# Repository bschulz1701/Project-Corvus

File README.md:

# Project-Corvus
Designs for multiple lab voltage/current sensor variations

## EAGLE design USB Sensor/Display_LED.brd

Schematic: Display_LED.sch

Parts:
BT1: AACLIP; BAT_AA_BK-92
C1, C2: C-EU12PFC0402; C0402
C3, C4, C11, C12: 0.1uF; C0603
C5, C10, C13: 1uF; C0603
C6: 10uF; C0805
C7: 10pF; C0603
C8, C9: 4.7uF; C0805
D1, D2, D3, D4, D5, D6, D7, D8, D9, D10, D11, D12, D13: LED0603; LED_0603
DS1, DS2: YSD-439AK2B-35; 7-SEGMENT-4DIGIT-YOUNGSUN
H1, H2, H3, H4, H5: MOUNTING_HOLE2_NP; 2_56
ISP1, ISP2, ISP3: AVRISP-6; AVRISP
J1: CONN_2X2MIRCOFIT_RT; 2X2_MICROFIT_RT
L1: INDUCTORMAPI_3X3; WE-MAPI(3X3)
Q1, Q2, Q3, Q4, Q13, Q14, Q15, Q16: MOSFET-NCH-2N7002P; SOT23-3
Q5: MOSFET-NCH-ZXMN3B14FTA; SOT23-3
R1, R2, R25: R-EU_10KR0603; R0603
R3, R4, R5, R6, R7, R8, R9, R10, R22, R24: 100k; R0603
R11, R37, R45: 10k; R0603
R12, R13, R14, R15, R16, R17, R18, R19, R20, R21, R26, R27, R28, R29, R30, R31, R32, R33, R35, R36, R38, R39, R46, R47, R48, R49, R50, R51, R52, R53, R54, R55: R-EU_330R0603; R0603
R23: 316k; R0603
R34: 330R; R0603
R40: R-EU_1KR0603; R0603
S1: DIP_8219_GULL; 219-8_GULLWING_DIP-CTS
S2, S3, S4: BUTTON6X6; SWITCH_6MM
S5: SPDTOS1020; OS102011MS2QN1
U1: ATMEGA644M; MLF44-TH
U2: SN74HC165PW; TSSOP16
U4, U7: ATMEGA48PMLF; MLF32-5X5
U5: TPS61021A; DSG0008A
XTAL1: CRYSTAL8MHZ5X3.2; CRYSTAL_5X3.2_2-SMD

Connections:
3V3: C3.1, C4.1, C5.1, C7.1, C8.1, C9.1, C10.1, C11.1, C12.1, C13.1, ISP1.2 (VCC), ISP2.2 (VCC), ISP3.2 (VCC), J1.1, R1.2, R2.2, R3.2, R4.2, R5.2, R6.2, R7.2, R8.2, R9.2, R10.2, R11.2, R23.2, R25.2, R35.2, R37.2, R45.2, U1.5 (VCC), U1.17 (VCC), U1.27 (AVCC), U1.29 (AREF), U1.38 (VCC), U2.16 (VCC), U4.4 (VCC), U4.6 (VCC), U4.18 (AVCC), U4.20 (AREF), U5.3 (VOUT), U5.4 (VOUT), U7.4 (VCC), U7.6 (VCC), U7.18 (AVCC), U7.20 (AREF)
!RESET: ISP1.5 (RST), R37.1, U1.4 (RESET)
!RESET_A: ISP2.5 (RST), R11.1, U4.29 ((PCINT14/!RESET!)PC6)
!RESET_B: ISP3.5 (RST), R45.1, U7.29 ((PCINT14/!RESET!)PC6)
B0: R3.1, S1.16, U2.11 (A)
B1: R4.1, S1.15, U2.12 (B)
B2: R5.1, S1.14, U2.13 (C)
B3: R6.1, S1.13, U2.14 (D)
B4: R7.1, S1.12, U2.3 (E)
B5: R8.1, S1.11, U2.4 (F)
B6: R9.1, S1.10, U2.5 (G)
B7: R10.1, S1.9, U2.6 (H)
BAT: BT1.POS@1 (+), BT1.POS@2 (+), C6.1, L1.P$1 (1), Q5.1 (G), R34.2, R40.2, S5.1 (O), U5.8 (VIN)
BAT_SENSE: R40.1, U1.37 ((PCINT0/ADC0)PA0)
BOOST_EN: R22.2, S5.2, U5.5 (EN)
DIP_CLK: U1.32 ((PCINT5/ADC5)PA5), U2.2 (CLK)
DIP_LD: U1.31 ((PCINT6/ADC6)PA6), U2.1 (SH/!LD)
DIP_OUT: U1.33 ((PCINT4/ADC4)PA4), U2.9 (QH)
DISP_SEL_A: R1.1, S2.1, S2.2, U1.25 ((PCINT22/TOSC1)PC6)
DISP_SEL_B: R2.1, S3.1, S3.2, U1.26 ((PCINT23/TOSC2)PC7)
DISP_STAT_D1_A: R28.2, U1.14 ((PCINT29/OC1A)PD5)
DISP_STAT_D1_B: R32.2, U1.22 ((PCINT19/TMS)PC3)
DISP_STAT_D2_A: R29.2, U1.13 ((PCINT28/OC1B)PD4)
DISP_STAT_D2_B: R33.2, U1.21 ((PCINT18/TCK)PC2)
DISP_STAT_I_A: R27.2, U1.15 ((PCINT30/OC2B/ICP)PD6)
DISP_STAT_I_B: R31.2, U1.23 ((PCINT20/TDO)PC4)
DISP_STAT_V_A: R26.2, U1.16 ((PCINT31/OC2A)PD7)
DISP_STAT_V_B: R30.2, U1.24 ((PCINT21/TDI)PC5)
DIS_A1: DS1.14 (A), R12.1
DIS_A2: DS2.14 (A), R46.1
DIS_B1: DS1.16 (B), R13.1
DIS_B2: DS2.16 (B), R47.1
DIS_C1: DS1.13 (C), R14.1
DIS_C2: DS2.13 (C), R48.1
DIS_COL1: DS1.12 (COL-C), R20.1
DIS_COL2: DS2.12 (COL-C), R54.1
DIS_D1: DS1.3 (D), R15.1
DIS_D2: DS2.3 (D), R49.1
DIS_DIG1_1: DS1.1 (DIG1), Q1.3 (D)
DIS_DIG1_2: DS2.1 (DIG1), Q13.3 (D)
DIS_DIG2_1: DS1.2 (DIG2), Q2.3 (D)
DIS_DIG2_2: DS2.2 (DIG2), Q14.3 (D)
DIS_DIG3_1: DS1.6 (DIG3), Q3.3 (D)
DIS_DIG3_2: DS2.6 (DIG3), Q15.3 (D)
DIS_DIG4_1: DS1.8 (DIG4), Q4.3 (D)
DIS_DIG4_2: DS2.8 (DIG4), Q16.3 (D)
DIS_DP1: DS1.7 (DP), R19.1
DIS_DP2: DS2.7 (DP), R53.1
DIS_E1: DS1.5 (E), R16.1
DIS_E2: DS2.5 (E), R50.1
DIS_F1: DS1.11 (F), R17.1
DIS_F2: DS2.11 (F), R51.1
DIS_G1: DS1.15 (G), R18.1
DIS_G2: DS2.15 (G), R52.1
DIS_POS1: DS1.9 (APOS-C), R21.1
DIS_POS2: DS2.9 (APOS-C), R55.1
FB: C7.2, R23.1, R24.2, U5.2 (FB)
GND: C1.1, C2.1, C3.2, C4.2, C5.2, C6.2, C8.2, C9.2, C10.2, C11.2, C12.2, C13.2, D1.CATHODE, D2.CATHODE, D3.CATHODE, D4.CATHODE, D5.CATHODE, D6.CATHODE, D7.CATHODE, D8.CATHODE, D10.CATHODE, D11.CATHODE, D12.CATHODE, D13.CATHODE, DS1.4 (COL-A), DS1.10 (APOS-A), DS2.4 (COL-A), DS2.10 (APOS-A), ISP1.6 (GND), ISP2.6 (GND), ISP3.6 (GND), J1.2, Q1.2 (S), Q2.2 (S), Q3.2 (S), Q4.2 (S), Q5.2 (S), Q13.2 (S), Q14.2 (S), Q15.2 (S), Q16.2 (S), R22.1, R24.1, S1.1, S1.2, S1.3, S1.4, S1.5, S1.6, S1.7, S1.8, S2.3, S2.4, S3.3, S3.4, S4.3, S4.4, S5.3 (S), U1.6 (GND), U1.18 (GND), U1.28 (GND), U1.39 (GND), U1.TH (EXP), U2.8 (GND), U2.10 (SER), U4.3 (GND), U4.5 (GND), U4.21 (GND), U4.TH (GND), U5.1 (AGND), U5.EP@1 (PGND), U5.EP@2 (PGND), U5.EP@3 (PGND), U7.3 (GND), U7.5 (GND), U7.21 (GND), U7.TH (GND)
HOLD: R25.1, S4.1, S4.2, U1.30 ((PCINT7/ADC7)PA7)
MCU_A1: R12.2, U4.32 ((PCINT18/INT0)PD2)
MCU_A2: R46.2, U7.32 ((PCINT18/INT0)PD2)
MCU_B1: R13.2, U4.1 ((PCINT19/INT1)PD3)
MCU_B2: R47.2, U7.1 ((PCINT19/INT1)PD3)
MCU_C1: R14.2, U4.2 ((PCINT20/XCK/T0)PD4)
MCU_C2: R48.2, U7.2 ((PCINT20/XCK/T0)PD4)
MCU_COL1: R20.2, U4.12 ((PCINT0/CLKO/ICP1)PB0)
MCU_COL2: R54.2, U7.12 ((PCINT0/CLKO/ICP1)PB0)
MCU_D1: R15.2, U4.9 ((PCINT21/OC0B/T1)PD5)
MCU_D2: R49.2, U7.9 ((PCINT21/OC0B/T1)PD5)
MCU_DIG1_1: Q1.1 (G), U4.26 ((PCINT11/ADC3)PC3)
MCU_DIG1_2: Q13.1 (G), U7.26 ((PCINT11/ADC3)PC3)
MCU_DIG2_1: Q2.1 (G), U4.25 ((PCINT10/ADC2)PC2)
MCU_DIG2_2: Q14.1 (G), U7.25 ((PCINT10/ADC2)PC2)
MCU_DIG3_1: Q3.1 (G), U4.24 ((PCINT9/ADC1)PC1)
MCU_DIG3_2: Q15.1 (G), U7.24 ((PCINT9/ADC1)PC1)
MCU_DIG4_1: Q4.1 (G), U4.23 ((PCINT8/ADC0)PC0)
MCU_DIG4_2: Q16.1 (G), U7.23 ((PCINT8/ADC0)PC0)
MCU_DP1: R19.2, U4.14 ((PCINT2/!SS!/OC1B)PB2)
MCU_DP2: R53.2, U7.14 ((PCINT2/!SS!/OC1B)PB2)
MCU_E1: R16.2, U4.10 ((PCINT22/OC0A/AIN0)PD6)
MCU_E2: R50.2, U7.10 ((PCINT22/OC0A/AIN0)PD6)
MCU_F1: R17.2, U4.11 ((PCINT23/AIN1)PD7)
MCU_F2: R51.2, U7.11 ((PCINT23/AIN1)PD7)
MCU_G1: R18.2, U4.7 ((PCINT6/XTAL1/TOSC1)PB6)
MCU_G2: R52.2, U7.7 ((PCINT6/XTAL1/TOSC1)PB6)
MCU_POS1: R21.2, U4.13 ((PCINT1/OC1A)PB1)
MCU_POS2: R55.2, U7.13 ((PCINT1/OC1A)PB1)
MISO: ISP1.1 (MISO), U1.2 ((PCINT14/MISO)PB6)
MISO_A: ISP2.1 (MISO), U4.16 ((PCINT4/MISO)PB4)
MISO_B: ISP3.1 (MISO), U7.16 ((PCINT4/MISO)PB4)
MOSI: ISP1.4 (MOSI), U1.1 ((PCINT13/MOSI)PB5)
MOSI_A: ISP2.4 (MOSI), U4.15 ((PCINT3/OC2A/MOSI)PB3)
MOSI_B: ISP3.4 (MOSI), U7.15 ((PCINT3/OC2A/MOSI)PB3)
unnamed: D1.ANODE, R26.1
unnamed: D2.ANODE, R27.1
unnamed: D3.ANODE, R28.1
unnamed: D4.ANODE, R29.1
unnamed: D5.ANODE, R30.1
unnamed: D6.ANODE, R31.1
unnamed: D7.ANODE, R32.1
unnamed: D8.ANODE, R33.1
unnamed: D10.ANODE, R35.1
unnamed: BT1.NEG@1 (-), BT1.NEG@2 (-), D9.ANODE, Q5.3 (D)
unnamed: D9.CATHODE, R34.1
unnamed: D12.ANODE, R38.1
unnamed: C2.2, U1.8 (XTAL1), XTAL1.OSC1 (1)
unnamed: D11.ANODE, R36.1
unnamed: C1.2, U1.7 (XTAL2), XTAL1.OSC2 (2)
unnamed: D13.ANODE, R39.1
PG: R36.2, U1.36 ((PCINT1/ADC1)PA1)
RX1: U1.10 ((PCINT25/TXD0)PD1), U4.30 ((PCINT16/RXD)PD0)
RX2: U1.12 ((PCINT27/INT1)PD3), U7.30 ((PCINT16/RXD)PD0)
SCK: ISP1.3 (SCK), U1.3 ((PCINT15/SCK)PB7)
SCK_A: ISP2.3 (SCK), U4.17 ((PCINT5/SCK)PB5)
SCK_B: ISP3.3 (SCK), U7.17 ((PCINT5/SCK)PB5)
SCL: J1.3, U1.19 ((PCINT16/SCL)PC0)
SDA: J1.4, U1.20 ((PCINT17/SDA)PC1)
STAT1: R39.2, U1.35 ((PCINT2/ADC2)PA2)
STAT2: R38.2, U1.34 ((PCINT3/ADC3)PA3)
SW: L1.P$2 (2), U5.6 (SW), U5.7 (SW)
TX1: U1.9 ((PCINT24/RXD0)PD0), U4.31 ((PCINT17/TXD)PD1)
TX2: U1.11 ((PCINT26/INT0)PD2), U7.31 ((PCINT17/TXD)PD1)

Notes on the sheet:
Allow for additional bulk capacitance if needed
BAT - Analog PG - DO DIP_LD - DO DIP_CLK - DO DIP_OUT - DI DISP_SEL_A - DI DISP_SEL_B - DI HOLD - DI STAT1 - DO STAT2- DO

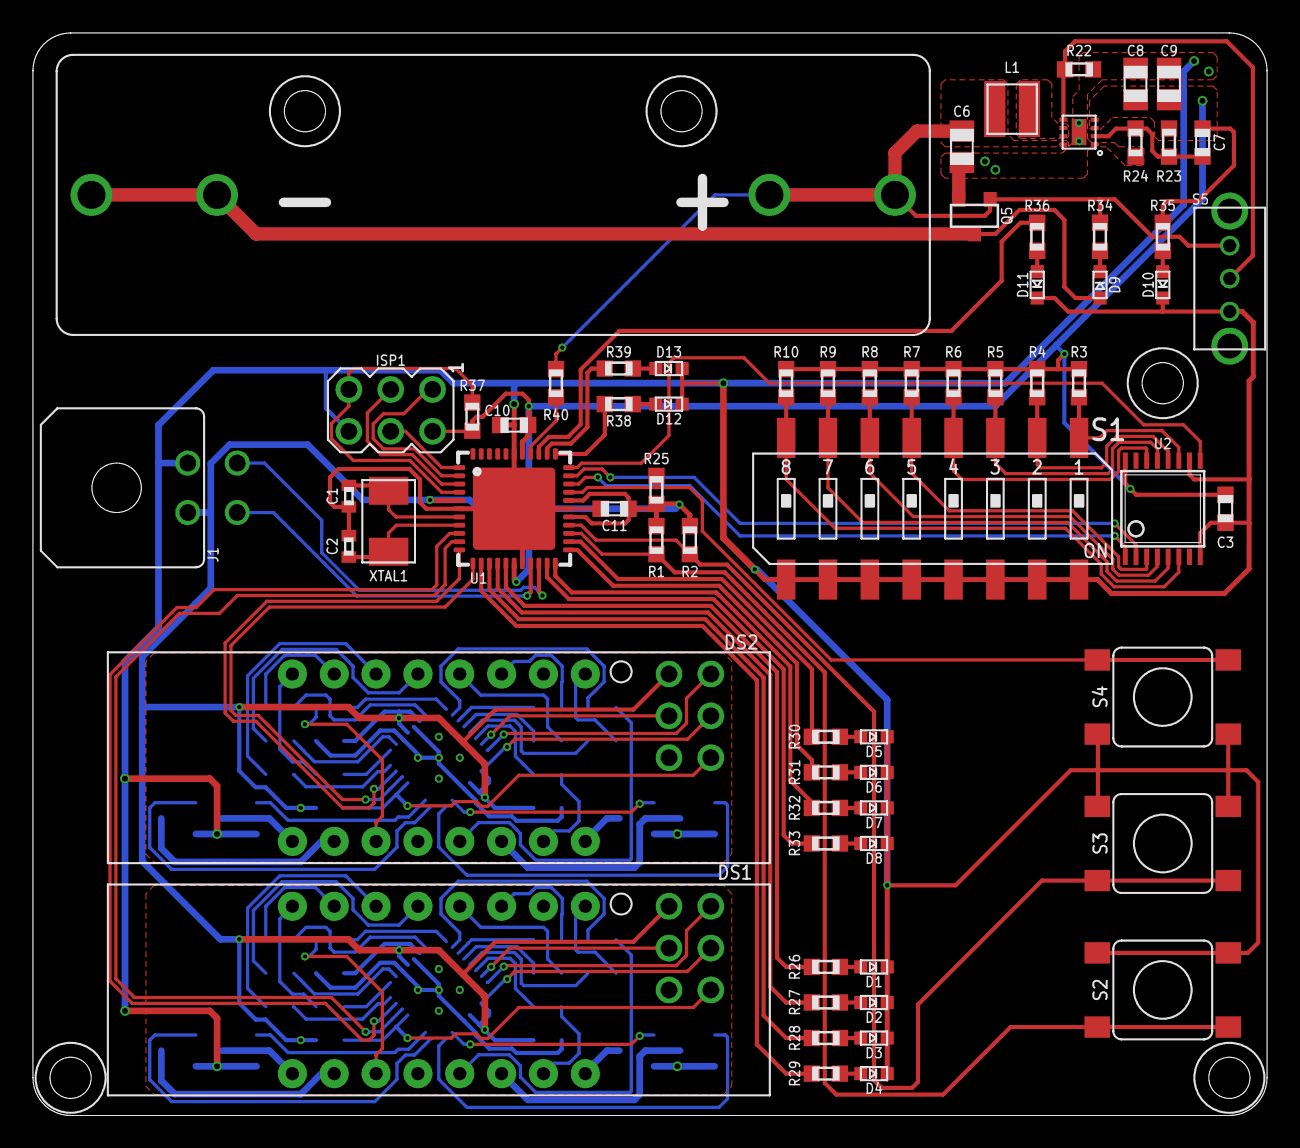
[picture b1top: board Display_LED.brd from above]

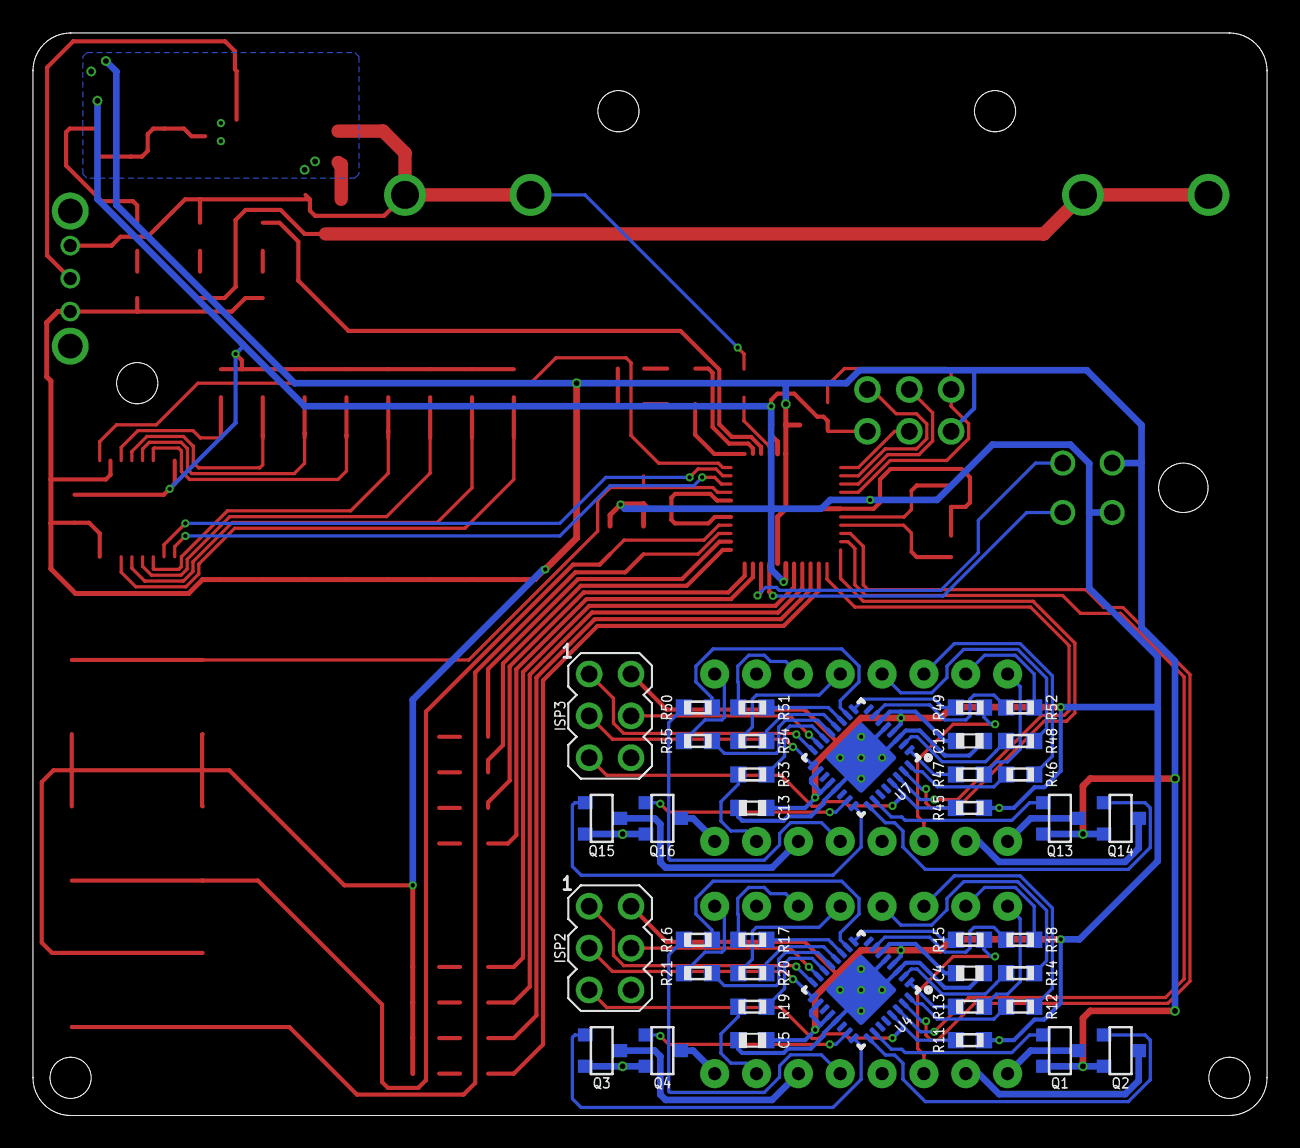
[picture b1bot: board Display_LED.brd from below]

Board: 2 copper layers, 74.9 x 65.7 mm, 110 parts (38 on the bottom side), 122 nets.

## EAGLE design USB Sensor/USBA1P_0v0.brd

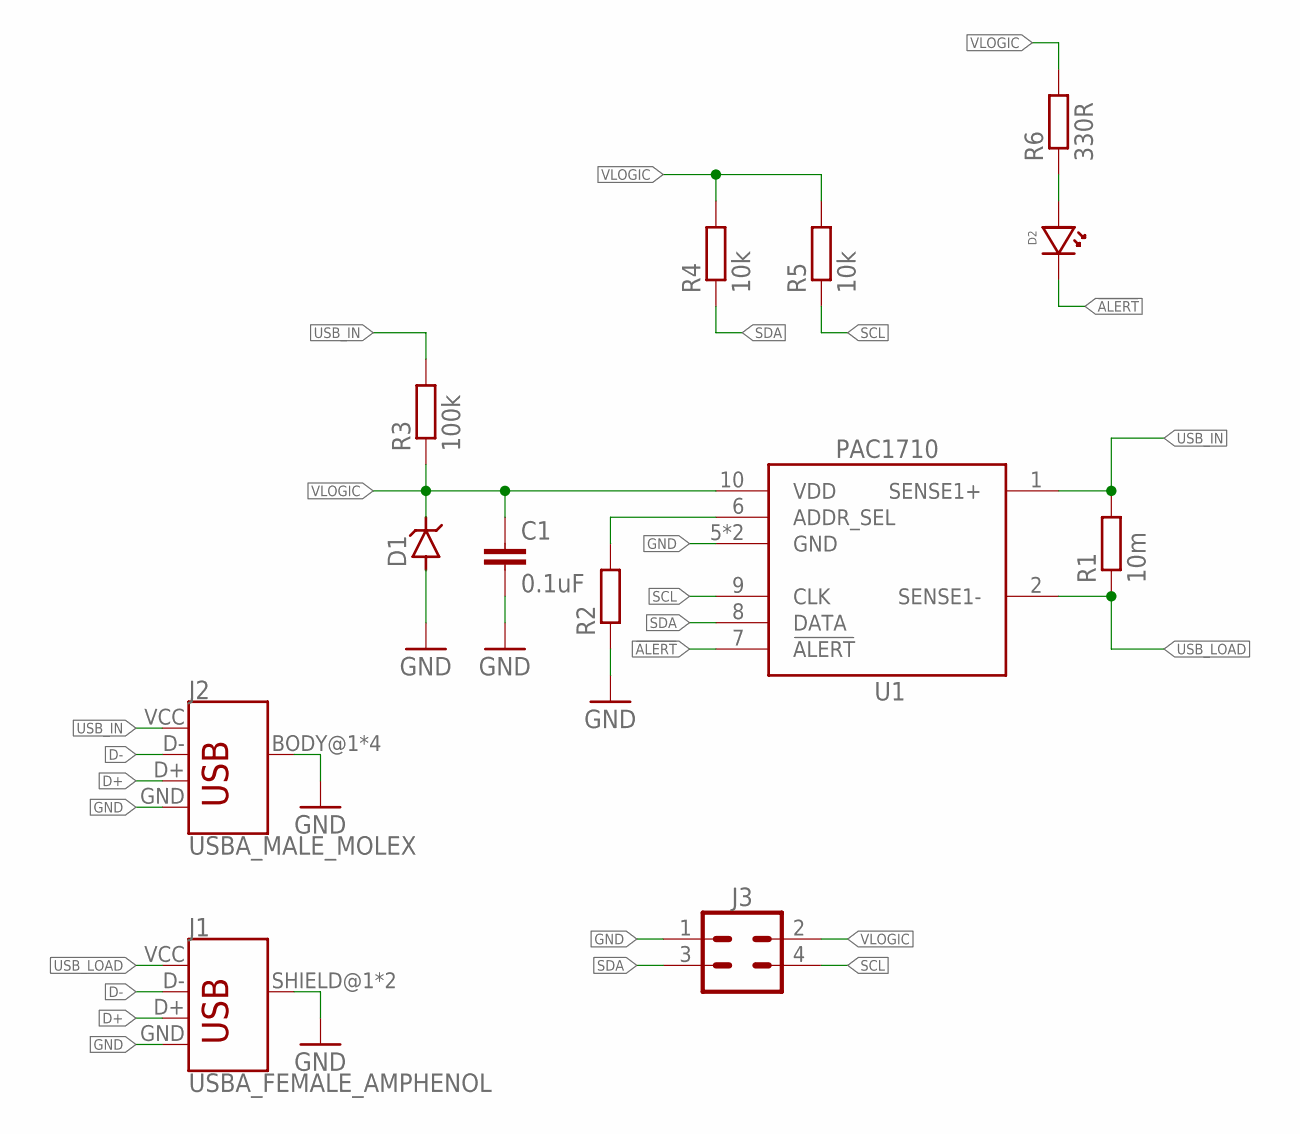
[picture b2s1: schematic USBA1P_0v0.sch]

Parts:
C1: 0.1uF; C0603
D1: DIODE_ZENERSOD-123; SOD-123
D2: LED1206_BOTTOM; LED_1206_BOTTOM
J1: USBA_FEMALE_AMPHENOL; USB_A_FEMALE_AMPHENOL
J2: USBA_MALE_MOLEX; USB_A_MALE_0480372200
J3: CONN_2X2MIRCOFIT_RT; 2X2_MICROFIT_RT
R1: 10m; R0805
R2: R-EU_R0603; R0603
R3: 100k; R0603
R4, R5: 10k; R0603
R6: 330R; R0603
U1: PAC1710; VDFN-10

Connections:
!ALERT: D2.CATHODE, U1.7 (!ALERT)
D+: J1.D+, J2.D+
D-: J1.D-, J2.D-
GND: C1.2, D1.ANODE (A), J1.GND, J1.SHIELD@1 (SHIELD), J1.SHIELD@2 (SHIELD), J2.BODY@1 (SHIELD), J2.BODY@2 (SHIELD), J2.BODY@3 (SHIELD), J2.BODY@4 (SHIELD), J2.GND, J3.1, R2.1, U1.5 (GND), U1.EP (GND)
unnamed: R2.2, U1.6 (ADDR_SEL)
unnamed: D2.ANODE, R6.1
SCL: J3.4, R5.1, U1.9 (CLK)
SDA: J3.3, R4.1, U1.8 (DATA)
USB_IN: J2.VCC (VBUS), R1.2, R3.2, U1.1 (SENSE1+)
USB_LOAD: J1.VCC (VBUS), R1.1, U1.2 (SENSE1-)
VLOGIC: C1.1, D1.CAT (C), J3.2, R3.1, R4.2, R5.2, R6.2, U1.10 (VDD)

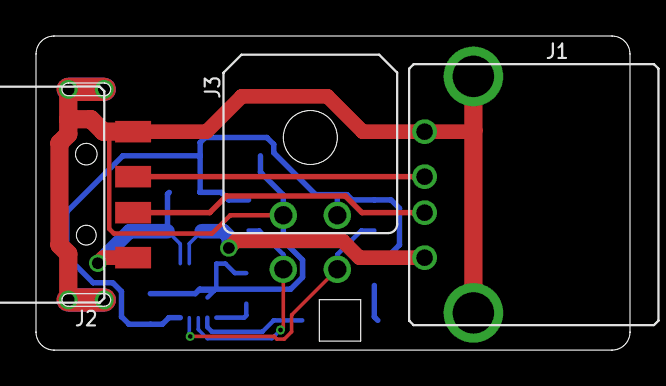
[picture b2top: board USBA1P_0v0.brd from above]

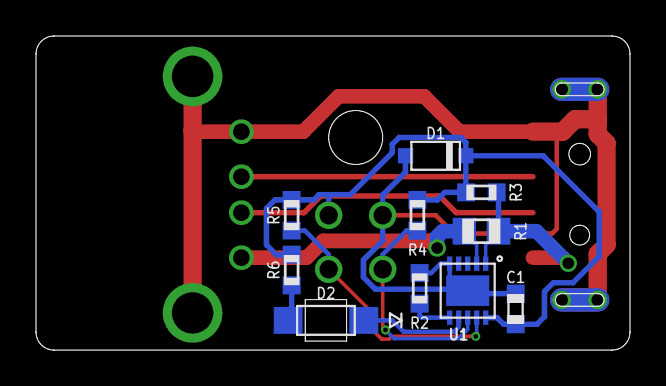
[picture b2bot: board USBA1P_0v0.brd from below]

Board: 2 copper layers, 33.0 x 17.4 mm, 13 parts (10 on the bottom side), 11 nets.

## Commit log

2021-02-27 Added Micro USB and USB A versions
    Added functionally complete Micro USB and USB A version, need final review before order.
2021-02-27 Add Sub-ALPHA Display module
    Extreme preliminary Display module work
2021-03-03 Continued layout of display module
    Preliminary placement done, major layout remaining
2021-03-04 Display layout complete, review required
    Layout of display module is complete, should be reviewed before sending to fab
2021-03-09 Added Molex and 3.0 USB options
    Added completed layouts for the Molex port and the USB 3.0 port
2021-03-09 Minor cleanup for USBA1P and USBm1P
    Cleanup to part naming and layout for A1P and micro setups
2021-03-09 Generated gerbers for fab
    Generated gerbers for LED display, USB3A1P, USBA1P, USBm1P, all version v0.0
2021-03-09 Fixed solder paste issue on LED Display
    Fixed solder paste issue (overlap) on the ATMEGA48P packages on the LED Display board
